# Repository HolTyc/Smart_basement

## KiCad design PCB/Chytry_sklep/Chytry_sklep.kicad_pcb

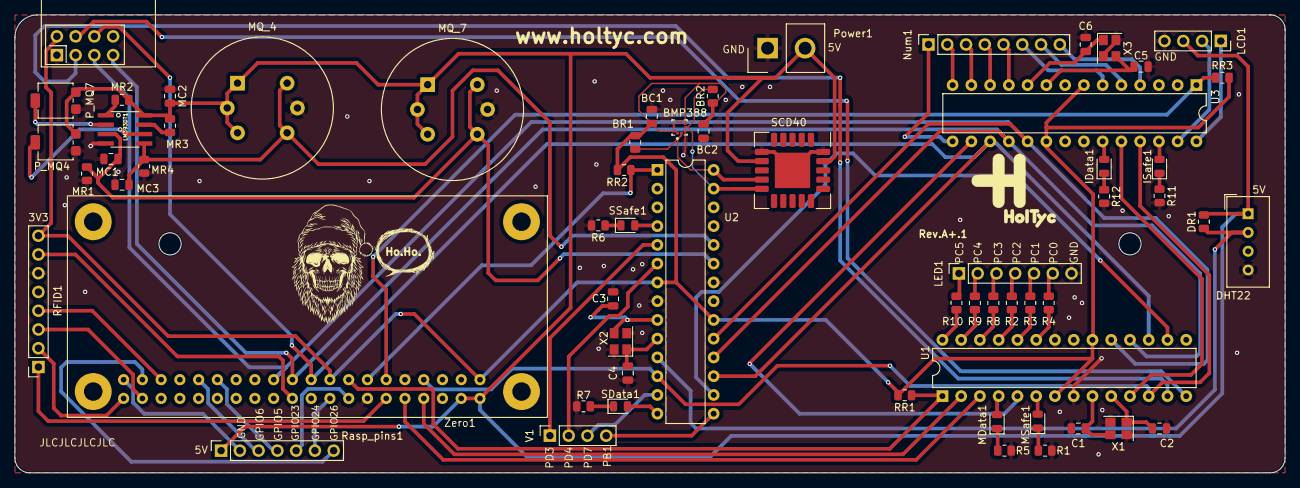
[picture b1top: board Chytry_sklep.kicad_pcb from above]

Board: 2 copper layers, 172.0 x 62.0 mm, 62 parts (0 on the bottom side), 81 nets.

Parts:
BC1, BC2: 100nF; C_0805_2012Metric
BMP388: BMP388
BR1, BR2: 4.7K; R_0805_2012Metric
C1, C2, C3, C4, C5, C6: 10p; C_0805_2012Metric
DHT22: DHT11; Aosong_DHT11_5.5x12.0_P2.54mm
DR1: 10k; R_0805_2012Metric
IData1: LED; LED_0805_2012Metric
ISafe1: LED; LED_0805_2012Metric
LCD1: Conn_01x04_Pin; PinSocket_1x04_P2.54mm_Vertical
LED1: Conn_01x07; PinSocket_1x07_P2.54mm_Vertical
LM393DT1: 0; LM393DT
MC1, MC2, MC3: 100nF; C_0805_2012Metric
MData1: LED; LED_0805_2012Metric
MQ_4: MQ-4; MQ-6
MQ_7: MQ-7; MQ-6
MR1, MR2, MR3, MR4: 10K; R_0805_2012Metric
MSafe1: LED; LED_0805_2012Metric
NRF1: NRF24L01_Breakout; nRF24L01_Breakout
Num1: Conn_01x08_Pin; PinSocket_1x08_P2.54mm_Vertical
P_MQ4, P_MQ7: TC33X-2-103E; Potentiometer_Bourns_3314G_Vertical
Power1: Conn_01x02_Pin; Samtec_HPM-02-01-x-S_Straight_1x02_Pitch5.08mm
R1, R2, R3, R4, R5, R6, R7, R8, R9, R10, R11, R12: 220; R_0805_2012Metric
RFID1: Conn_01x08_Pin; PinSocket_1x08_P2.54mm_Vertical
RR1, RR2, RR3: 10k; R_0805_2012Metric
Rasp_pins1: Conn_01x07_Pin; PinSocket_1x07_P2.54mm_Vertical
SCD40: SCD40-D-R2; Sensirion_SCD4x-1EP_10.1x10.1mm_P1.25mm_EP4.8x4.8mm
SData1: LED; LED_0805_2012Metric
SSafe1: LED; LED_0805_2012Metric
U1, U2, U3: ATmega328-P; DIP-28_W7.62mm
V1: Volne_sensor; PinSocket_1x04_P2.54mm_Vertical
X1, X2, X3: 16Mhz; Crystal_SMD_3225-4Pin_3.2x2.5mm
Zero1: Raspberry_Pi_2_3; RaspberryPi_zero

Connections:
+3.3V: BC1.2, BC2.1, BMP388.1 (VDDIO), BMP388.5 (SDO), BMP388.10 (VDD), BR1.2, BR2.1, NRF1.2 (VCC), RFID1.8, RR1.2, RR2.2, RR3.2, U1.7 (VCC), U1.20 (AVCC), U2.7 (VCC), U2.20 (AVCC), U3.7 (VCC), U3.20 (AVCC), Zero1.1 (3V3), Zero1.17 (3V3)
+5V: DHT22.1 (VCC), DR1.2, LCD1.3, LM393DT1.8 (VCC), MC2.2, MQ_4.1 (B1), MQ_4.2 (VH+), MQ_4.3 (B2), MQ_7.1 (B1), MQ_7.2 (VH+), MQ_7.3 (B2), MR2.1, MR3.2, P_MQ4.1, P_MQ7.1, Power1.2, Rasp_pins1.1, SCD40.7 (VDD), SCD40.19 (VDD), Zero1.2 (5V), Zero1.4 (5V)
/Atmega_interface/CE_interface: U1.5 (PD3), U3.16 (PB2)
/Atmega_interface/Master_order: U1.11 (PD5), U3.24 (PC1)
/Atmega_interface/RST: RR3.1, U3.1 (~RESET/PC6), Zero1.11 (GPIO17)
/Atmega_interface/Safe_pin: U1.12 (PD6), U2.12 (PD6), U3.25 (PC2), Zero1.7 (GCLK0/GPIO4)
/Atmega_master/CE_sensor: U1.16 (PB2), U2.16 (PB2)
/Atmega_master/RST: RR1.1, U1.1 (~RESET/PC6), Zero1.15 (GPIO22)
/Atmega_sensor/RST: RR2.1, U2.1 (~RESET/PC6), Zero1.13 (GPIO27)
/RX: U1.2 (PD0), Zero1.8 (GPIO14/TXD)
/TX: U1.3 (PD1), Zero1.10 (GPIO15/RXD)
CE: NRF1.3 (CE), U1.13 (PD7)
CSN: NRF1.4 (~CSN), U1.14 (PB0)
D3: U2.5 (PD3), V1.1
D4: U2.6 (PD4), V1.2
D7: U2.13 (PD7), V1.3
D9: U2.15 (PB1), V1.4
GND: BC1.1, BC2.2, BMP388.3 (VSS), BMP388.8 (VSS), BMP388.9 (VSS), C1.1, C2.2, C3.2, C4.2, C5.2, C6.2, DHT22.4 (GND), LCD1.4, LED1.7, LM393DT1.4 (GND), MC1.1, MC2.1, MC3.1, MQ_4.5 (VH-), MQ_7.5 (VH-), MR1.2, MR4.2, NRF1.1 (GND), P_MQ4.3, P_MQ7.3, Power1.1, R1.2, R5.2, R6.2, R7.2, R11.2, R12.2, RFID1.6, SCD40.6 (GND), SCD40.20 (GND), SCD40.21 (GND), U1.8 (GND), U1.22 (GND), U2.8 (GND), U2.22 (GND), U3.8 (GND), U3.22 (GND), X1.2, X1.4, X2.2, X2.4, X3.2, X3.4, Zero1.9 (GND), Zero1.14 (GND)
GND1: Rasp_pins1.2, Zero1.39 (GND)
ISCL: LCD1.1, U3.28 (PC5)
ISDA: LCD1.2, U3.27 (PC4)
MISO: NRF1.7 (MISO), U1.18 (PB4), U2.18 (PB4), U3.18 (PB4), Zero1.21 (MISO0/GPIO9)
MOSI: NRF1.6 (MOSI), U1.17 (PB3), U2.17 (PB3), U3.17 (PB3), Zero1.19 (MOSI0/GPIO10)
MPC0: IData1.2 (A), U3.23 (PC0)
MQ_4_D: LM393DT1.5 (IN2+), MC3.2, MQ_4.4 (A2), MQ_4.6 (A1), MR4.1, U2.24 (PC1)
MQ_7_D: LM393DT1.3 (IN1+), MC1.2, MQ_7.4 (A2), MQ_7.6 (A1), MR1.1, U2.23 (PC0)
unnamed: DHT22.2 (IO), DR1.1, U2.11 (PD5)
unnamed: IData1.1 (K), R12.1
unnamed: ISafe1.2 (A), U3.26 (PC3)
unnamed: ISafe1.1 (K), R11.1
unnamed: LM393DT1.1 (OUT1), MR2.2
unnamed: LM393DT1.7 (OUT2), MR3.1
unnamed: MData1.2 (A), U1.4 (PD2)
unnamed: MData1.1 (K), R5.1
unnamed: MSafe1.2 (A), U1.6 (PD4)
unnamed: MSafe1.1 (K), R1.1
unnamed: Num1.1, U3.15 (PB1)
unnamed: Num1.2, U3.14 (PB0)
unnamed: Num1.3, U3.13 (PD7)
unnamed: Num1.4, U3.12 (PD6)
unnamed: Num1.5, U3.11 (PD5)
unnamed: Num1.6, U3.6 (PD4)
unnamed: Num1.7, U3.5 (PD3)
unnamed: Num1.8, U3.4 (PD2)
unnamed: RFID1.1, Zero1.12 (GPIO18/PWM0)
unnamed: RFID1.2, Zero1.40 (GPIO21/SCLK1)
unnamed: RFID1.3, Zero1.38 (GPIO20/MOSI1)
unnamed: RFID1.4, Zero1.35 (GPIO19/MISO1)
unnamed: RFID1.7, Zero1.22 (GPIO25)
unnamed: Rasp_pins1.3, Zero1.31 (GCLK2/GPIO6)
unnamed: Rasp_pins1.4, Zero1.29 (GCLK1/GPIO5)
unnamed: Rasp_pins1.5, Zero1.16 (GPIO23)
unnamed: Rasp_pins1.6, Zero1.18 (GPIO24)
unnamed: Rasp_pins1.7, Zero1.37 (GPIO26)
unnamed: SData1.2 (A), U2.14 (PB0)
unnamed: R7.1, SData1.1 (K)
unnamed: SSafe1.2 (A), U2.4 (PD2)
unnamed: R6.1, SSafe1.1 (K)
unnamed: R4.1, U1.23 (PC0)
unnamed: R3.1, U1.24 (PC1)
unnamed: R2.1, U1.25 (PC2)
unnamed: R8.1, U1.26 (PC3)
unnamed: R9.1, U1.27 (PC4)
unnamed: R10.1, U1.28 (PC5)
unnamed: C1.2, U1.9 (XTAL1/PB6), X1.3
unnamed: C2.1, U1.10 (XTAL2/PB7), X1.1
unnamed: C3.1, U2.9 (XTAL1/PB6), X2.3
unnamed: C4.1, U2.10 (XTAL2/PB7), X2.1
unnamed: C5.1, U3.9 (XTAL1/PB6), X3.3
unnamed: C6.1, U3.10 (XTAL2/PB7), X3.1
PC0: LED1.6, R4.2
PC1: LED1.5, R3.2
PC2: LED1.4, R2.2
PC3: LED1.3, R8.2
PC4: LED1.2, R9.2
PC5: LED1.1, R10.2
POT1: LM393DT1.2 (IN1-), P_MQ7.2
POT2: LM393DT1.6 (IN2-), P_MQ4.2
SCK: NRF1.5 (SCK), U1.19 (PB5), U2.19 (PB5), U3.19 (PB5), Zero1.23 (SCLK0/GPIO11)
SCL: BMP388.2 (SCK), BR1.1, SCD40.9 (SCL), U2.28 (PC5)
SDA: BMP388.4 (SDI), BR2.2, SCD40.10 (SDA), U2.27 (PC4)

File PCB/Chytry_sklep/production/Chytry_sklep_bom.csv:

Comment,Designator,Footprint,LCSC Part Number
100nF,"BC1, BC2, MC1, MC2, MC3",Capacitor_SMD:C_0805_2012Metric,C49678
BMP388,BMP388,Bosh:BMP388,C779278
4.7K,"BR1, BR2",Resistor_SMD:R_0805_2012Metric,C17673
10p,"C1, C2, C3, C4, C5, C6",Capacitor_SMD:C_0805_2012Metric,C157608
LED,"IData1, MData1, SData1",LED_SMD:LED_0805_2012Metric,C2297
LED,"ISafe1, MSafe1, SSafe1",LED_SMD:LED_0805_2012Metric,C2296
0,LM393DT1,ST:LM393DT,C32901
MQ-7,MQ_7,Sensor:MQ-6,C242495
10K_Potentiometer,"P_MQ4, P_MQ7",Potentiometer_SMD:Potentiometer_Bourns_3314G_Vertical,C780220
220,"R1, R2, R3, R4, R5, R6, R7, R8, R9, R10, R11, R12",Resistor_SMD:R_0805_2012Metric,C17557
10k,"MR1, MR2, MR3, MR4, RR1, RR2, RR3, DR1",Resistor_SMD:R_0805_2012Metric,C17414
16Mhz,"X1, X2, X3",Crystal:Crystal_SMD_3225-4Pin_3.2x2.5mm,C13738

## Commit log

2025-02-28 Git init
2025-02-28 File init
2025-03-04 Revision A+ 1
2025-03-22 Last old version
    Created SklepWan and starting to work on STM32 smart_basement and STM32 SklepWan Devboard
2025-12-28 Finally functional version
